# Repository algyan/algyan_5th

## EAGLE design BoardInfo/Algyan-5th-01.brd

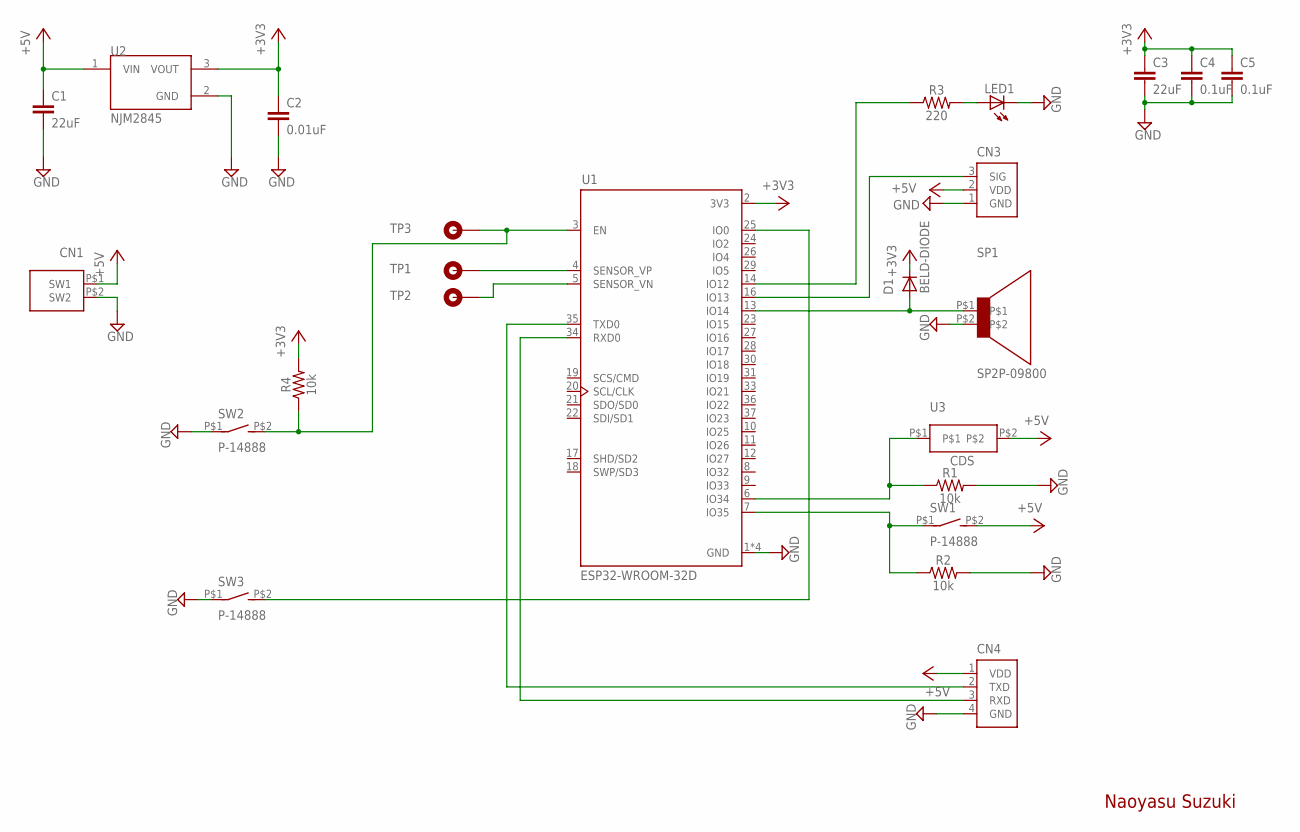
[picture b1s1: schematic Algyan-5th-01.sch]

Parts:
C1, C3: 22uF; 1210
C2: 0.01uF; 0603
C4, C5: 0.1uF; 0603
CN1: SW－WP; SP2
CN3: MIL3; ML3
CN4: ESP-UART; ML4
D1: BELD-DIODE; DB2S40600L
LED1: LED3216; 3216
R1, R2, R4: 10k; 0603
R3: 220; 0603
SP1: SP2P-09800; P-09800
SW1, SW2, SW3: P-14888
TP1, TP2, TP3: TPHOLE; TP-HOLE
U1: ESP32-WROOM-32D; MODULE_ESP32-WROOM-32D
U2: NJM2845; TO252
U3: CDS

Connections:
+3V3: C2.1, C3.1, C4.1, C5.1, D1.P$1 (K), R4.2, U1.2 (3V3), U2.3 (VOUT)
+5V: C1.1, CN1.P$1 (SW1), CN3.2 (VDD), CN4.1 (VDD), SW1.P$2 (S), U2.1 (VIN), U3.P$2
GND: C1.2, C2.2, C3.2, C4.2, C5.2, CN1.P$2 (SW2), CN3.1 (GND), CN4.4 (GND), LED1.P$1 (C), R1.2, R2.2, SP1.P$2, SW2.P$1, SW3.P$1, U1.1 (GND), U1.15 (GND), U1.38 (GND), U1.39 (GND), U2.2 (GND)
unnamed: R1.1, U1.6 (IO34), U3.P$1
unnamed: CN3.3 (SIG), U1.16 (IO13)
unnamed: R2.1, SW1.P$1, U1.7 (IO35)
unnamed: D1.P$2 (A), SP1.P$1, U1.13 (IO14)
unnamed: R4.1, SW2.P$2 (S), TP3.1, U1.3 (EN)
unnamed: TP1.1, U1.4 (SENSOR_VP)
unnamed: TP2.1, U1.5 (SENSOR_VN)
unnamed: CN4.2 (TXD), U1.35 (TXD0)
unnamed: CN4.3 (RXD), U1.34 (RXD0)
unnamed: R3.1, U1.14 (IO12)
unnamed: LED1.P$2 (A), R3.2
unnamed: SW3.P$2 (S), U1.25 (IO0)

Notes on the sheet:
Naoyasu Suzuki

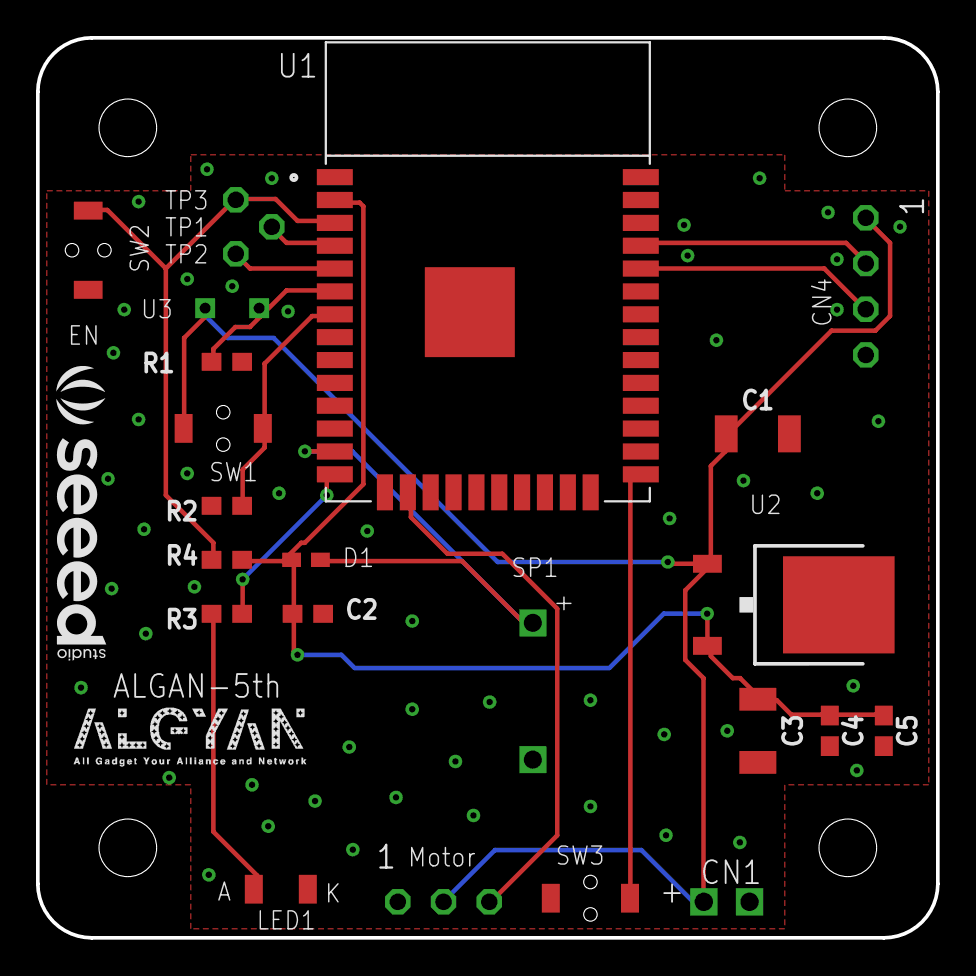
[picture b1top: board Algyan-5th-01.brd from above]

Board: 2 copper layers, 50.0 x 50.0 mm, 24 parts (0 on the bottom side), 15 nets.

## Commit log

2020-07-09 ハードウェアチェック用ソフト、新規コミット
2020-07-09 markup 文法が間違っていてみにくかったため修正
2020-07-13 Create BoardInfo.txt
    1.Create
2020-07-14 Add Case 3D model files
2020-07-23 説明文を大幅に修正
2020-07-23 誤記修正。
2020-07-23 誤記修正
2020-07-24 はんだ付けの事前準備を登録
2020-07-24 JPGファイルリンクを修正
2020-07-24 テスト用Appへのリンクを修正
2020-07-24 パーツリストのPDFへのリンク追加
2020-07-25 はんだ付けマニュアルを更新
2020-07-26 ショットキーバリアダイオードのアノード/カソードの説明誤記訂正
2020-07-26 パーツリストにはんだ付け順序と極性のある部品に「極性注意」を追記
2020-08-02 CdS and SW change connect 5V -> 3.3V
